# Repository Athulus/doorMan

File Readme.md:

## Door Man ## 

A project in micropython that will unlock or lock a door based on an mqtt feed.

It will also push lock status to the mqtt feed when lock is changed manually.

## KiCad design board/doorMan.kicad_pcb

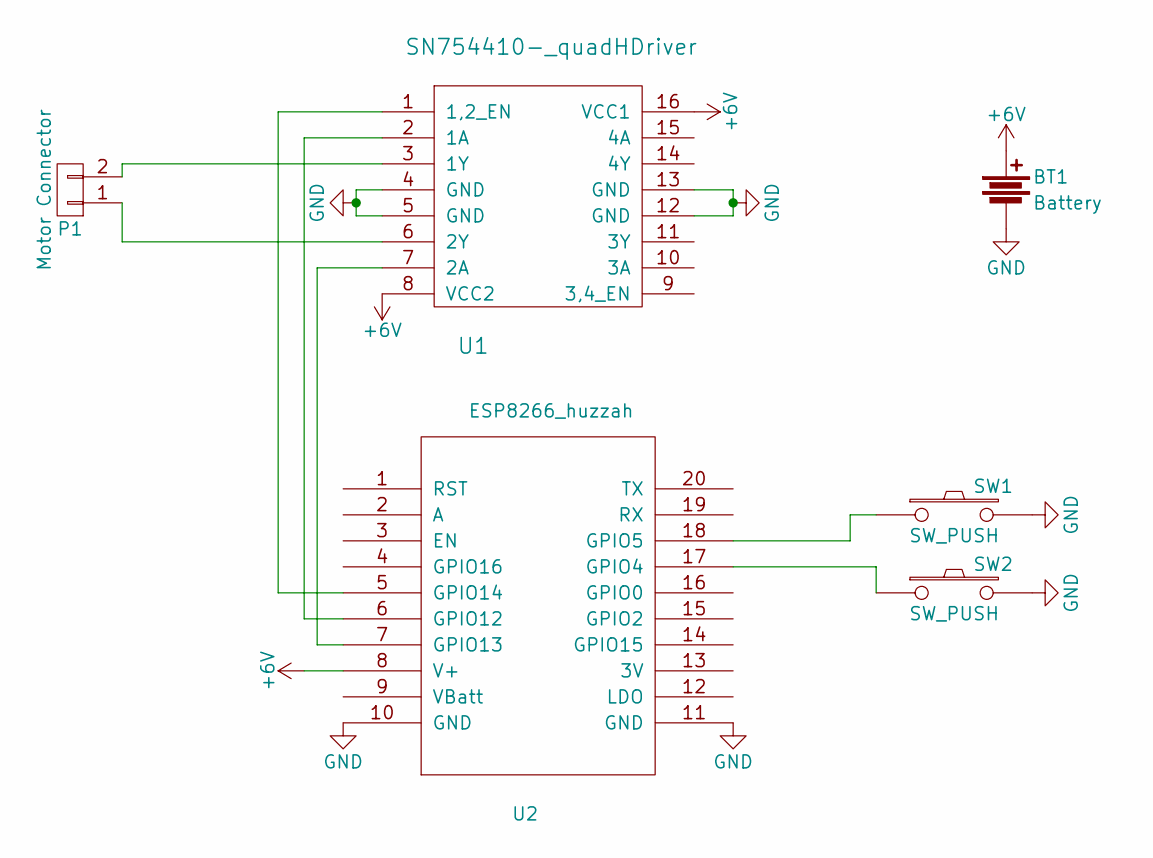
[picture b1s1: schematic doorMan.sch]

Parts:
BT1: Battery; Pin_Header_Straight_1x02
P1: Motor Connector; Socket_Strip_Straight_1x02
SW1, SW2: SW_PUSH; Socket_Strip_Straight_1x02
U1: SN754410-_quadHDriver; DIP-16_0_ELL
U2: ESP8266_huzzah; esp8266_socket_2x10

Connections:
+6V: BT1.1, U1.8 (VCC2), U1.16 (VCC1), U2.8 (V+)
GND: BT1.2, SW1.2, SW2.2, U1.4 (GND), U1.5 (GND), U1.12 (GND), U1.13 (GND), U2.10 (GND), U2.11 (GND)
unnamed: P1.1, U1.6 (2Y)
unnamed: P1.2, U1.3 (1Y)
unnamed: SW1.1, U2.18 (GPIO5)
unnamed: SW2.1, U2.17 (GPIO4)
unnamed: U1.1 (1,2_EN), U2.5 (GPIO14)
unnamed: U1.2 (1A), U2.6 (GPIO12)
unnamed: U1.7 (2A), U2.7 (GPIO13)

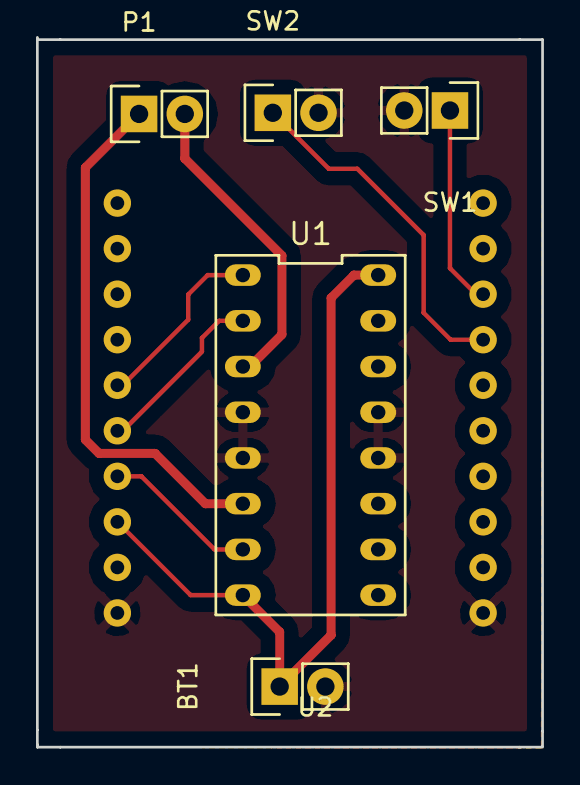
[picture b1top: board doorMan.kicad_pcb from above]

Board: 2 copper layers, 28.1 x 39.4 mm, 6 parts (0 on the bottom side), 9 nets.

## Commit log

2017-01-29 inital commit
2017-01-30 got mqtt client working. state machine for locking and unlocking implimented. stubbed out area where motor will do stuff
2017-02-08 putting functionality into a class
2017-02-08 class caused memory issues. refactored class code back into its original form and stuck it into the doorLock.py file. refactored main.py to use doorLock module
2017-02-28 adding board files
2017-03-31 Update Readme.md
    bold readme
2017-06-03 adding third flag for correct locking sequence
2017-06-03 added gitignore. fix some lint errors in doorLock
